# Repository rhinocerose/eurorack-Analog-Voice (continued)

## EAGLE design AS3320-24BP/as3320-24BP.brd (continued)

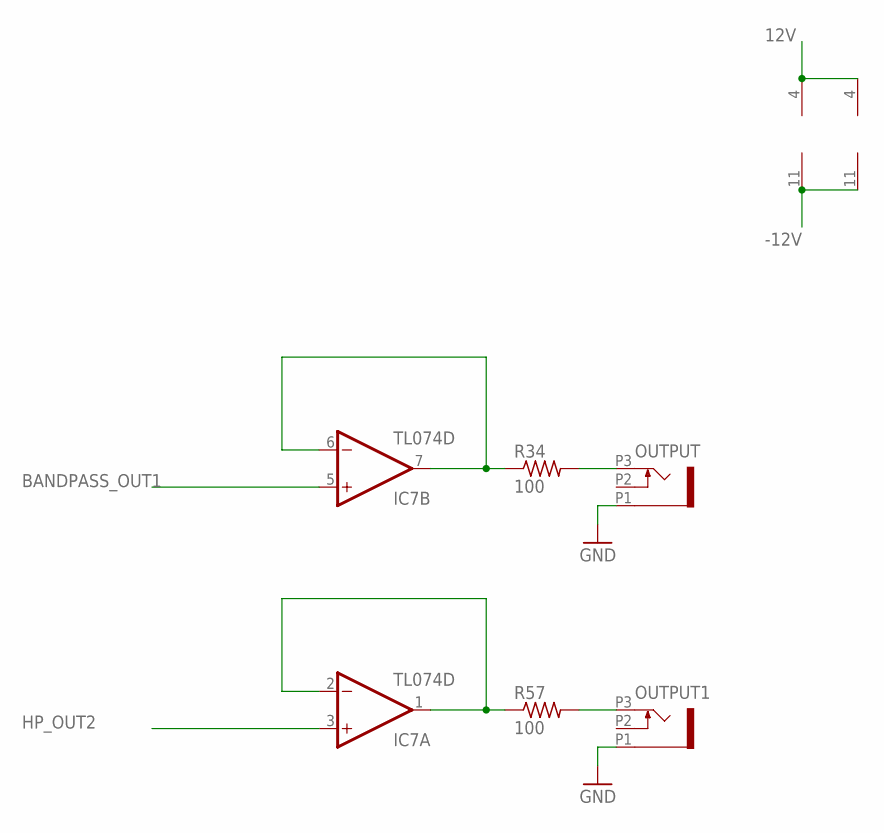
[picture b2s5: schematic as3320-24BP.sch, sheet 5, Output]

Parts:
IC7, IC8: TL074D; SO14
OUTPUT, OUTPUT1: PJ301_THONKICONN6; WQP_PJ_301M6
R34, R57: 100; GMSN_M0805

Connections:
12V: IC7.4 (V+), IC8.4 (V+); also elsewhere on the board
-12V: IC7.11 (V-), IC8.11 (V-); also elsewhere on the board
BANDPASS_OUT1: IC7.5 (+IN)
GND: OUTPUT.P1 (1), OUTPUT1.P1 (1); also elsewhere on the board
HP_OUT2: IC7.3 (+IN); also elsewhere on the board
unnamed: IC7.6 (-IN), IC7.7 (OUT), R34.1
unnamed: IC7.1 (OUT), IC7.2 (-IN), R57.1
unnamed: OUTPUT.P3 (3), R34.2
O2: OUTPUT1.P3 (3), R57.2

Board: 2 copper layers, 102 parts (23 on the bottom side), 66 nets, no tracks yet.

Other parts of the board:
U$2, U$3, U$4, U$5: MOUNTING_HOLE

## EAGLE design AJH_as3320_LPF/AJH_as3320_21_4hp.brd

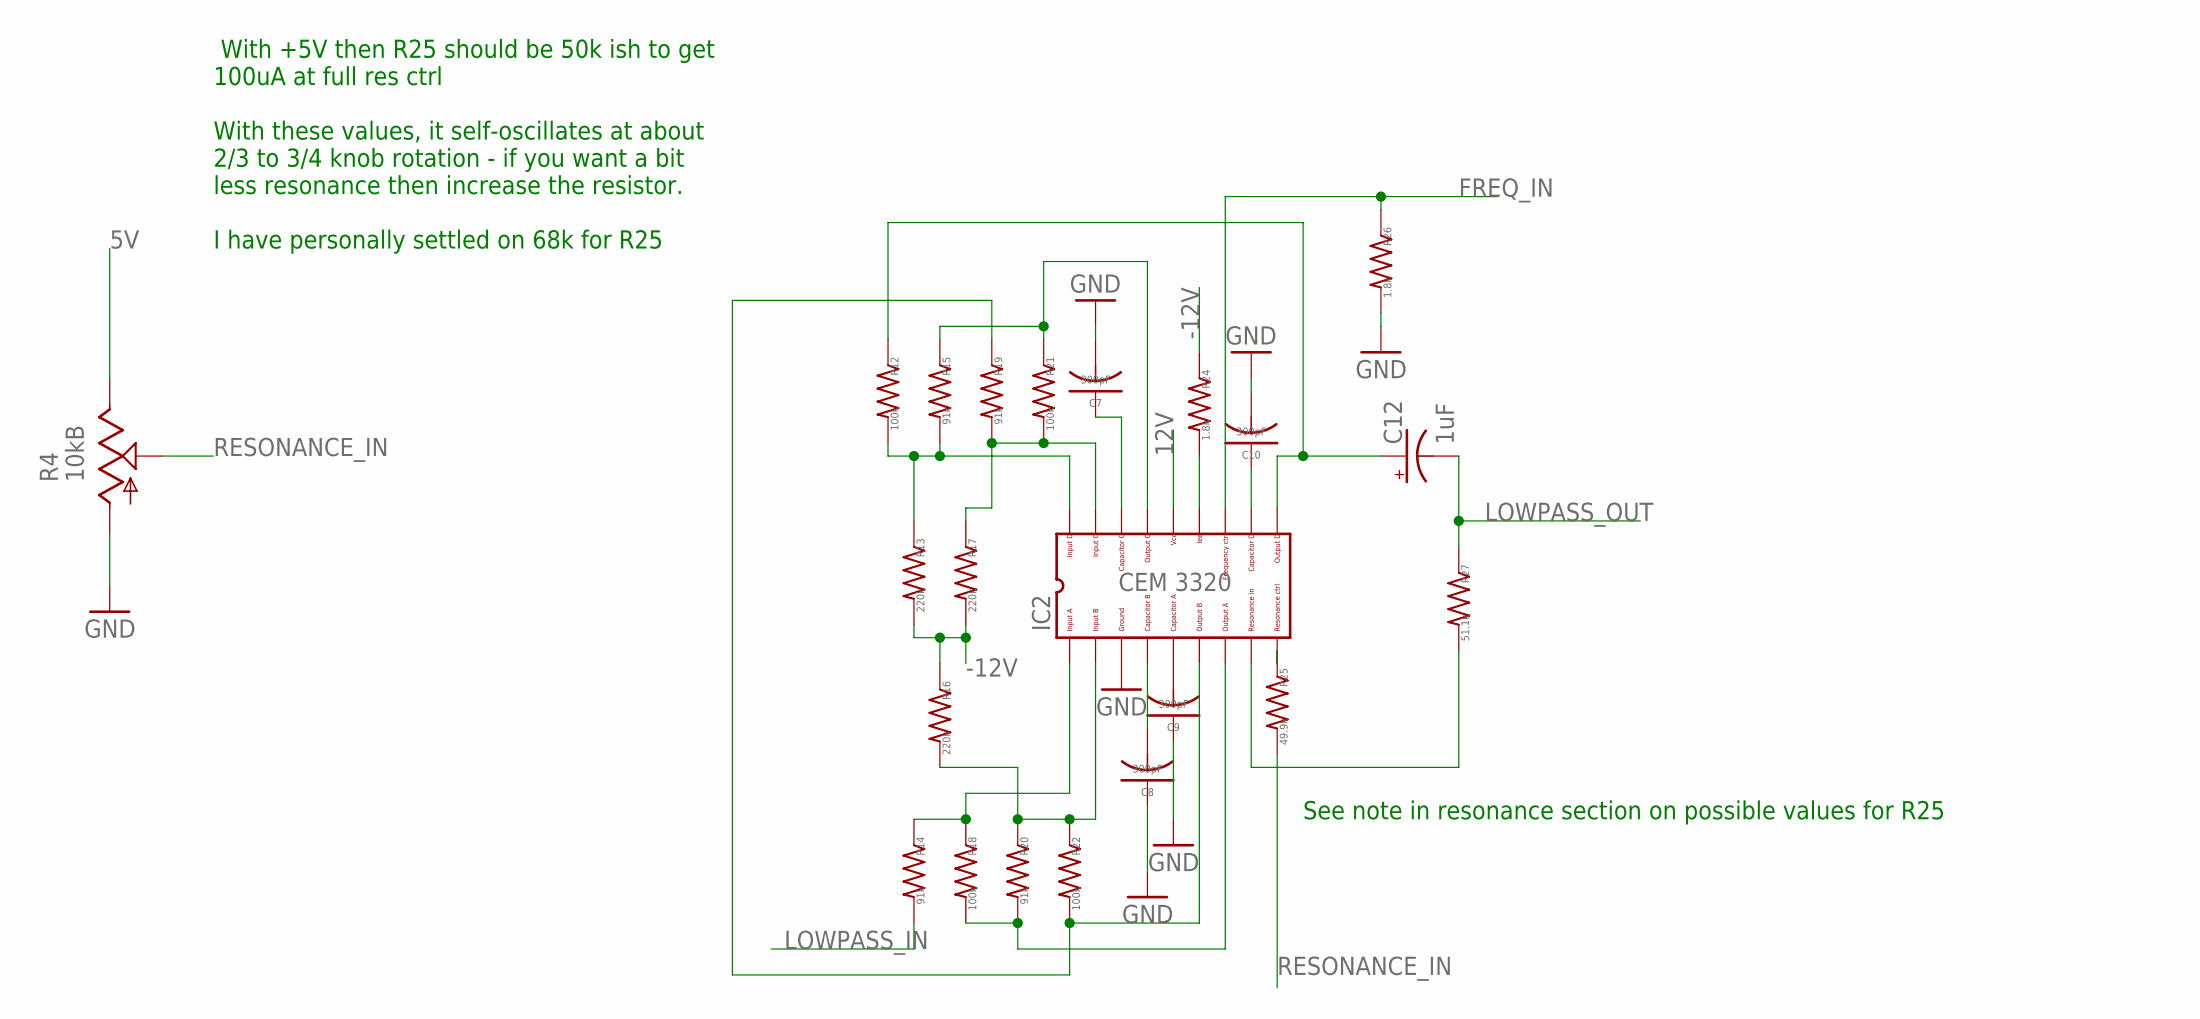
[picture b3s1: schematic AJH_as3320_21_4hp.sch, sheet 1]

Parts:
C7, C8, C9, C10: 300pF; C0603
C12: 1uF; PANASONIC_B
IC2: CEM3320QFN24; QFN24
R4: 10kB; ALPS_POT_VERTICAL
R12, R18, R21, R22: 100k; R0603
R13, R16, R17: 220k; R0603
R14, R15, R19, R20: 91k; R0603
R24, R26: 1.8k; R0603
R25: 49.9k; R0603
R27: 51.1k; R0603

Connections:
5V: R4.P$1 (E); also elsewhere on the board
12V: IC2.P$22 (14); also elsewhere on the board
-12V: R13.2, R16.1, R17.2, R24.1; also elsewhere on the board
FREQ_IN: IC2.P$19 (12), R26.1; also elsewhere on the board
GND: C7.2, C8.1, C9.1, C10.2, IC2.P$7 (3), R4.P$3 (A), R26.2; also elsewhere on the board
LOWPASS_IN: R14.2; also elsewhere on the board
LOWPASS_OUT: C12.-, R27.1; also elsewhere on the board
unnamed: IC2.P$3 (18), R12.2, R13.1, R15.2
unnamed: C7.1, IC2.P$24 (16)
unnamed: C8.2, IC2.P$8 (4)
unnamed: C9.2, IC2.P$9 (5)
unnamed: C10.1, IC2.P$17 (11)
unnamed: IC2.P$15 (9), R25.1
unnamed: IC2.P$4 (1), R14.1, R18.1
unnamed: IC2.P$12 (7), R18.2, R20.2
unnamed: IC2.P$11 (6), R19.1, R22.2
unnamed: IC2.P$23 (15), R15.1, R21.1
unnamed: C12.+, IC2.P$16 (10), R12.1
unnamed: IC2.P$14 (8), R27.2
unnamed: IC2.P$5 (2), R16.2, R20.1, R22.1
unnamed: IC2.P$2 (17), R17.1, R19.2, R21.2
unnamed: IC2.P$20 (13), R24.2
RESONANCE_IN: R4.P$2 (S), R25.2

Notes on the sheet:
With +5V then R25 should be 50k ish to get 100uA at full res ctrl With these values, it self-oscillates at about 2/3 to 3/4 knob rotation - if you want a bit less resonance then increase the resistor. I have personally settled on 68k for R25
See note in resonance section on possible values for R25

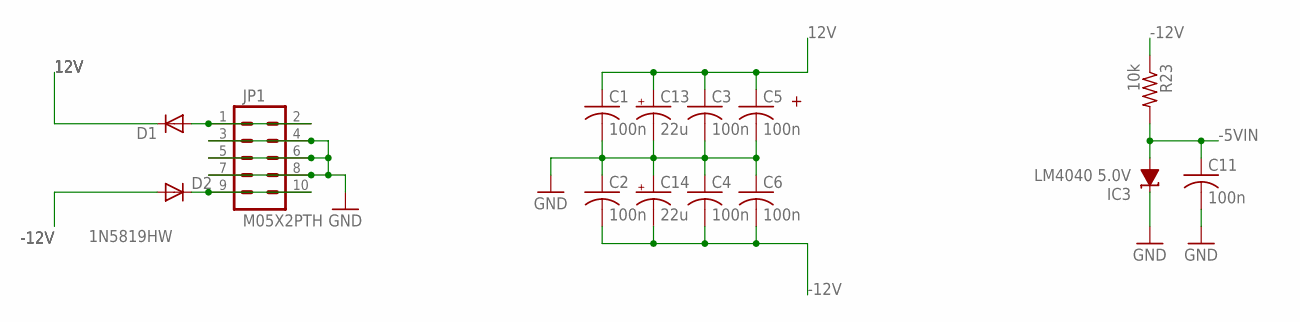
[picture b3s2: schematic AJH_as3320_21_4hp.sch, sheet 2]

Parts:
C1, C2, C3, C4, C5, C6, C11: 100n; C0603
C13, C14: 22u; PANASONIC_B
D1, D2: 1N5819HW; SOD123
IC3: LM4040 5.0V; DBZ_R-PDSO-G3
JP1: M05X2PTH; AVR_ICSP
R23: 10k; R0603

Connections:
12V: C1.1, C3.1, C5.1, C13.+, D1.C; also elsewhere on the board
-5VIN: C11.1, IC3.2 (A), R23.2; also elsewhere on the board
-12V: C2.2, C4.2, C6.2, C14.-, D2.A, R23.1; also elsewhere on the board
GND: C1.2, C2.1, C3.2, C4.1, C5.2, C6.1, C11.2, C13.-, C14.+, IC3.1 (C), JP1.3, JP1.4, JP1.5, JP1.6, JP1.7, JP1.8; also elsewhere on the board
unnamed: D1.A, JP1.1, JP1.2
unnamed: D2.C, JP1.9, JP1.10

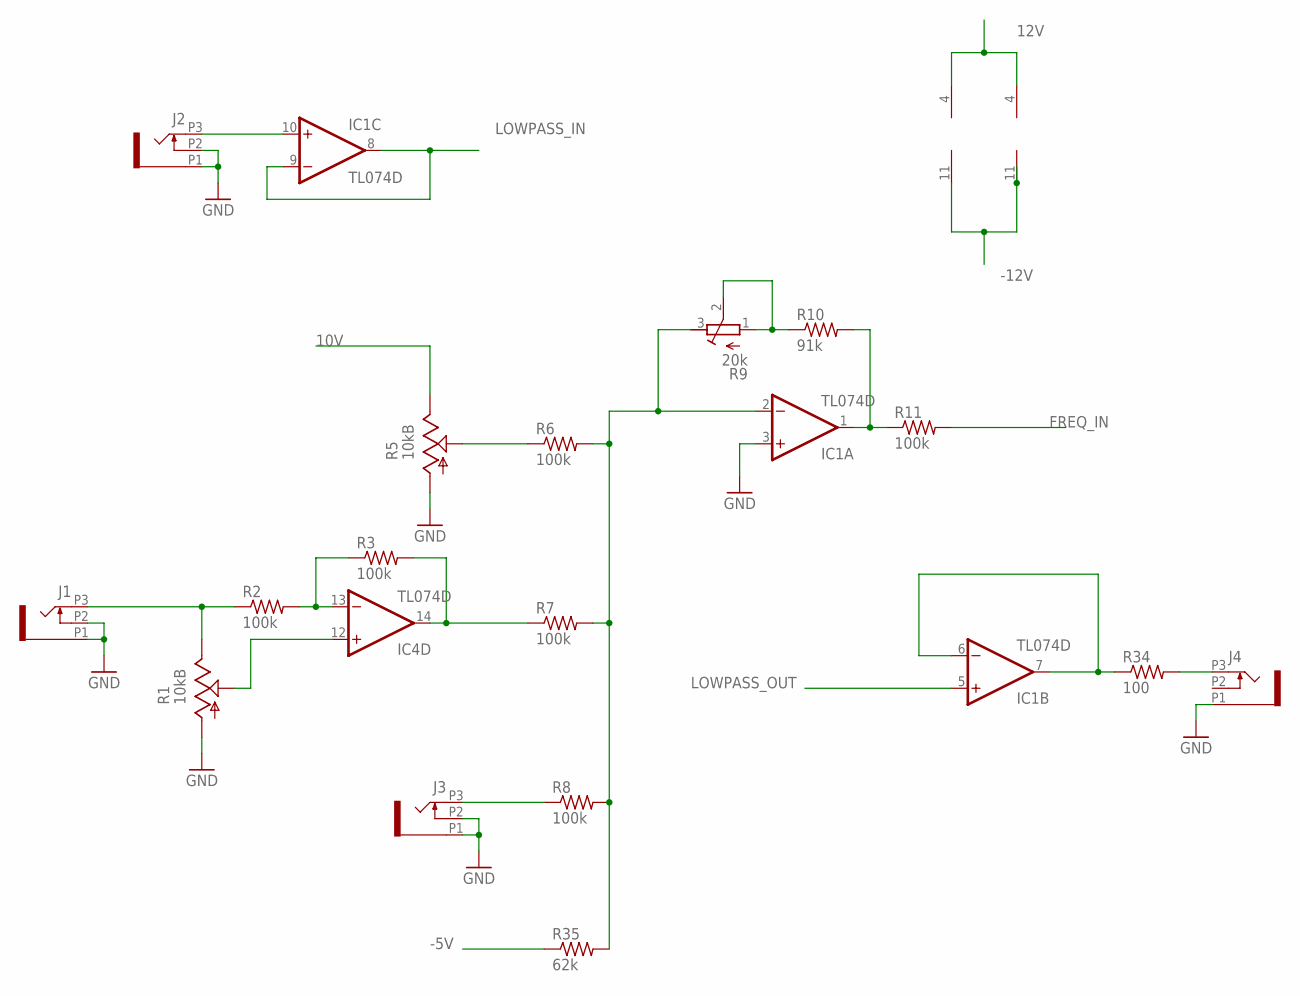
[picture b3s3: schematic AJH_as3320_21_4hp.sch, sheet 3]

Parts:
IC1, IC4: TL074D; SO14
J1, J2, J3, J4: PJ301_THONKICONN6; WQP_PJ_301M6
R1, R5: 10kB; ALPS_POT_VERTICAL
R2, R3, R6, R7, R8, R11: 100k; R0603
R9: 20k; RTRIM3296X
R10: 91k; R0603
R34: 100; R0603
R35: 62k; R0603

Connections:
10V: R5.P$1 (E); also elsewhere on the board
12V: IC1.4 (V+), IC4.4 (V+); also elsewhere on the board
-5V: R35.1; also elsewhere on the board
-12V: IC1.11 (V-), IC4.11 (V-); also elsewhere on the board
FREQ_IN: R11.2; also elsewhere on the board
GND: IC1.3 (+IN), J1.P1 (1), J1.P2 (2), J2.P1 (1), J2.P2 (2), J3.P1 (1), J3.P2 (2), J4.P1 (1), R1.P$3 (A), R5.P$3 (A); also elsewhere on the board
LOWPASS_IN: IC1.8 (OUT), IC1.9 (-IN); also elsewhere on the board
LOWPASS_OUT: IC1.5 (+IN); also elsewhere on the board
unnamed: IC1.6 (-IN), IC1.7 (OUT), R34.1
unnamed: IC4.12 (+IN), R1.P$2 (S)
unnamed: R5.P$2 (S), R6.1
unnamed: IC4.13 (-IN), R2.2, R3.1
unnamed: IC1.2 (-IN), R6.2, R7.2, R8.2, R9.3 (A), R35.2
unnamed: IC1.1 (OUT), R10.2, R11.1
unnamed: IC1.10 (+IN), J2.P3 (3)
unnamed: J3.P3 (3), R8.1
unnamed: J4.P3 (3), R34.2
unnamed: IC4.14 (OUT), R3.2, R7.1
unnamed: R9.1 (E), R9.2 (S), R10.1
unnamed: J1.P3 (3), R1.P$1 (E), R2.1

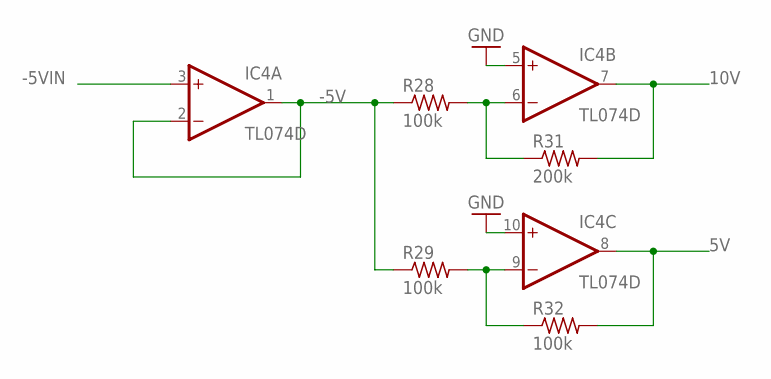
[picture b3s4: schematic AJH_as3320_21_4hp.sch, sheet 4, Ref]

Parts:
IC4: TL074D; SO14
R28, R29, R32: 100k; R0603
R31: 200k; R0603

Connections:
5V: IC4.8 (OUT), R32.2; also elsewhere on the board
10V: IC4.7 (OUT), R31.2; also elsewhere on the board
-5V: IC4.1 (OUT), IC4.2 (-IN), R28.1, R29.1; also elsewhere on the board
-5VIN: IC4.3 (+IN); also elsewhere on the board
GND: IC4.5 (+IN), IC4.10 (+IN); also elsewhere on the board
unnamed: IC4.9 (-IN), R29.2, R32.1
unnamed: IC4.6 (-IN), R28.2, R31.1

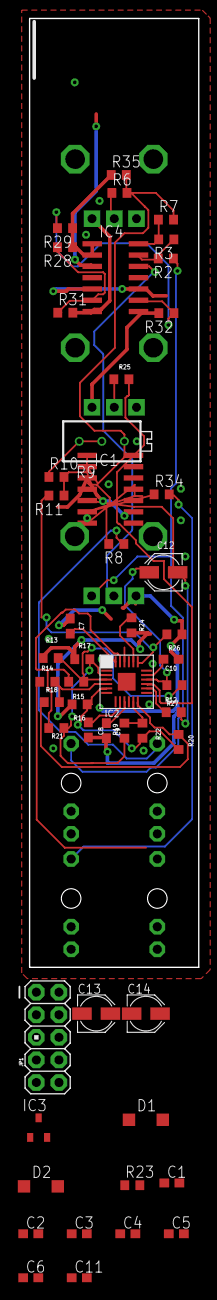
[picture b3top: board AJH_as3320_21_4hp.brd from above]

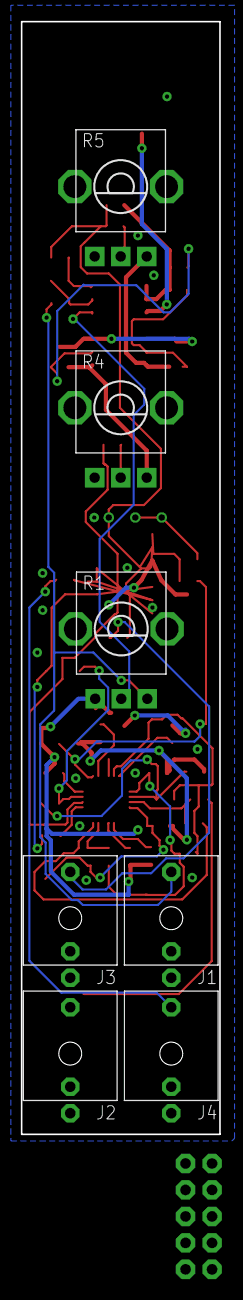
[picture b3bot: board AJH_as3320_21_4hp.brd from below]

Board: 2 copper layers, 19.0 x 106.8 mm, 58 parts (7 on the bottom side), 42 nets.

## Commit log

2020-06-06 Maded Multisheet and added input buffer
2020-06-06 Updated power to op-amps
2020-06-07 First Bandpass Circuit
2020-06-07 Changed name to Bandpass
2020-07-04 scematic for vowel processor
2020-07-19 Updated to resonance voltage control
2020-07-19 fixed resonance input routing
2021-04-22 adding work done on 24db BP
2025-08-12 Update submodules to track main branch
2025-08-12 Update submodules: set branch=main and fix URLs
2025-08-12 Update submodules: add branch=main and fix URLs
2025-08-13 Remove .gitmodules (no submodules exist)
